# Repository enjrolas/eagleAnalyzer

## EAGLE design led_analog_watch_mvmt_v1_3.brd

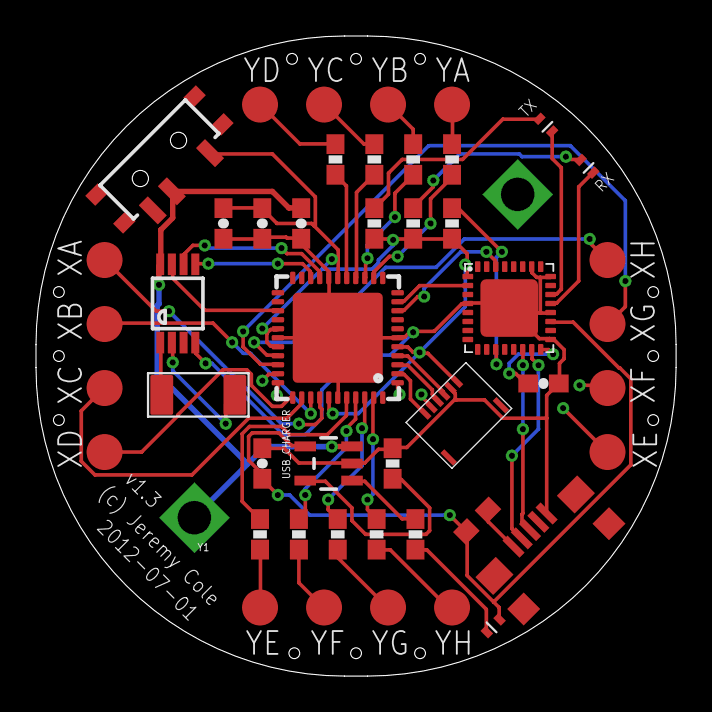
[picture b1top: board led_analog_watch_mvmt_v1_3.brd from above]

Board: 4 copper layers, 35.6 x 35.6 mm, 47 parts (1 on the bottom side), 51 nets.

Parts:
BAT1: 3V Li-Ion; BATTCON_245MM_PTH
C1, C2, C3, C4, C5: 0.1uF; 0603-CAP
CHLED: 0402
F1: 500mA; 0603
MCU: ATMEGA644M; MLF44-TH
R1, R11, R12: 330; 0603
R2, R3, R4, R5, R6, R7, R8, R9: 0603
R10, R13: 10k; 0603
RTC: DS1337UMAX; UMAX8
RXLED: 0402
S1: SWITCH-MA12R
TXLED: 0402
U$2: MOLEX_503480
USB_CHARGER: MCP73831; SOT23-5
USB_SERIAL: FT232RQ; QFN32
XA: TP20R
XB: TP20R
XC: TP20R
XD: TP20R
XE: TP20R
XF: TP20R
XG: TP20R
XH: TP20R
Y1: 32kHz; CRYSTAL-ABS10-SMD
YA: TP20R
YB: TP20R
YC: TP20R
YD: TP20R
YE: TP20R
YF: TP20R
YG: TP20R
YH: TP20R
µUSB: USB_MICROB_PLUG; USB_MICRO_B_TYCO

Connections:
GND: BAT1.2, C1.2, C2.2, C3.2, C4.2, C5.2, MCU.6, MCU.18, MCU.28, MCU.39, MCU.TH, R10.2, RTC.4, U$2.5, USB_CHARGER.2, USB_SERIAL.4, USB_SERIAL.17, USB_SERIAL.20, USB_SERIAL.24, USB_SERIAL.26, USB_SERIAL.EXP, µUSB.5
MISO: MCU.2, U$2.1
MOSI: MCU.1, U$2.2
unnamed: R1.2, USB_CHARGER.1
unnamed: R10.1, USB_CHARGER.5
unnamed: R2.2, YH.TP
unnamed: R3.2, YG.TP
unnamed: R4.2, YF.TP
unnamed: R5.2, YE.TP
unnamed: R6.2, YD.TP
unnamed: R7.2, YC.TP
unnamed: R8.2, YB.TP
unnamed: R9.2, YA.TP
unnamed: CHLED.2, R1.1
unnamed: R13.1, USB_SERIAL.11
unnamed: R12.1, RXLED.1
unnamed: RTC.2, Y1.X1
unnamed: RTC.1, Y1.X2
unnamed: R11.1, TXLED.1
unnamed: C5.1, USB_SERIAL.16
RST: MCU.4, U$2.4
RXD: MCU.9, USB_SERIAL.30
RXLED: RXLED.2, USB_SERIAL.21
SCK: MCU.3, U$2.3
SCL: MCU.19, RTC.6
SDA: MCU.20, RTC.5
SQW: MCU.25, RTC.7
TXD: MCU.10, USB_SERIAL.2
TXLED: TXLED.2, USB_SERIAL.22
USB_5V: C2.1, CHLED.1, F1.2, USB_CHARGER.4, USB_SERIAL.19
USB_N: USB_SERIAL.15, µUSB.2
USB_P: USB_SERIAL.14, µUSB.3
USB_UF: F1.1, µUSB.1
VBATT: BAT1.3, C1.1, RTC.8, S1.2, USB_CHARGER.3
VCC: C3.1, C4.1, MCU.5, MCU.17, MCU.27, MCU.29, MCU.38, R11.2, R12.2, R13.2, S1.3, U$2.6, USB_SERIAL.1
XA: MCU.37, XA.TP
XB: MCU.36, XB.TP
XC: MCU.35, XC.TP
XD: MCU.34, XD.TP
XE: MCU.33, XE.TP
XF: MCU.32, XF.TP
XG: MCU.31, XG.TP
XH: MCU.30, XH.TP
YA: MCU.13, R9.1
YB: MCU.14, R8.1
YC: MCU.15, R7.1
YD: MCU.16, R6.1
YE: MCU.40, R5.1
YF: MCU.41, R4.1
YG: MCU.42, R3.1
YH: MCU.43, R2.1

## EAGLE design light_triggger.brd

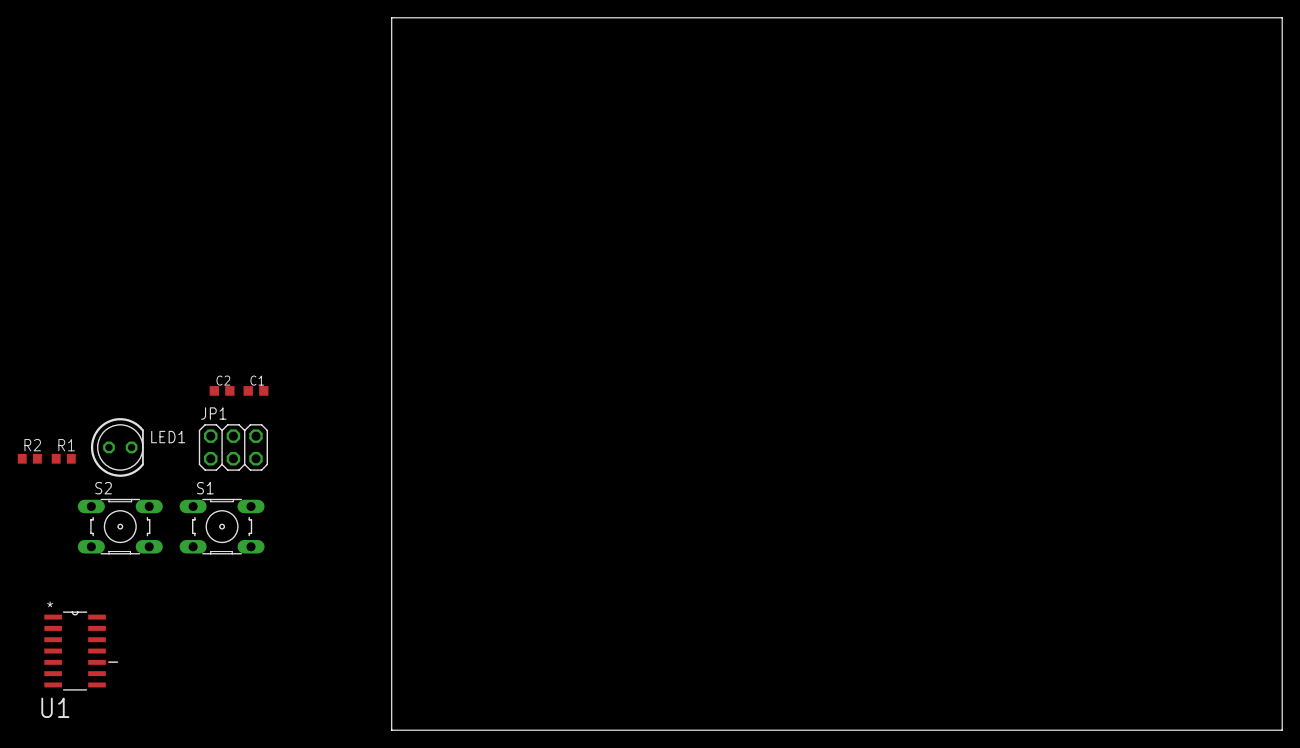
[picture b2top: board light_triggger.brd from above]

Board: 2 copper layers, 100.0 x 80.0 mm, 9 parts (0 on the bottom side), 8 nets, no tracks yet.

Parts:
C1, C2: C0603K
JP1: 2X03
LED1: LED5MM
R1, R2: R0603
S1, S2: B3F-10XX
U1: ATTINY24-20SSU; SOIC127P600X175-14N

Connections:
GND: C1.2, C2.2, JP1.6, S1.1, S1.2, S2.1, S2.2, U1.14
MISO: JP1.1, U1.5
MOSI: JP1.4, LED1.A, U1.3
unnamed: LED1.K, U1.8
unnamed: C2.1, R2.1, S2.3, S2.4, U1.7
RST: JP1.5, U1.4
SCK: C1.1, JP1.3, R1.1, S1.3, S1.4, U1.6
VCC: JP1.2, R1.2, R2.2, U1.1

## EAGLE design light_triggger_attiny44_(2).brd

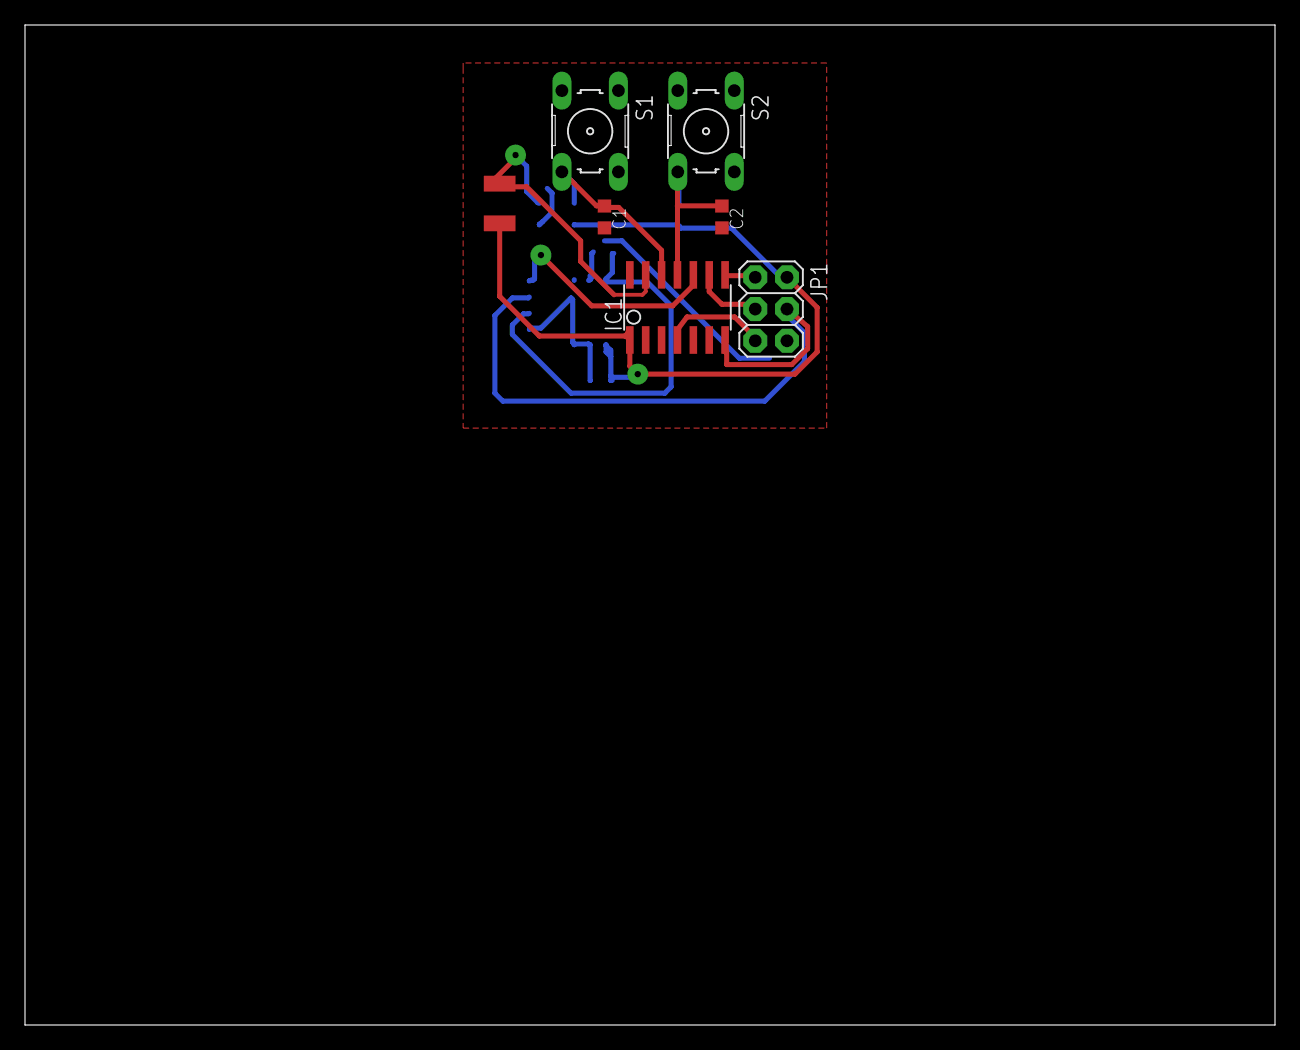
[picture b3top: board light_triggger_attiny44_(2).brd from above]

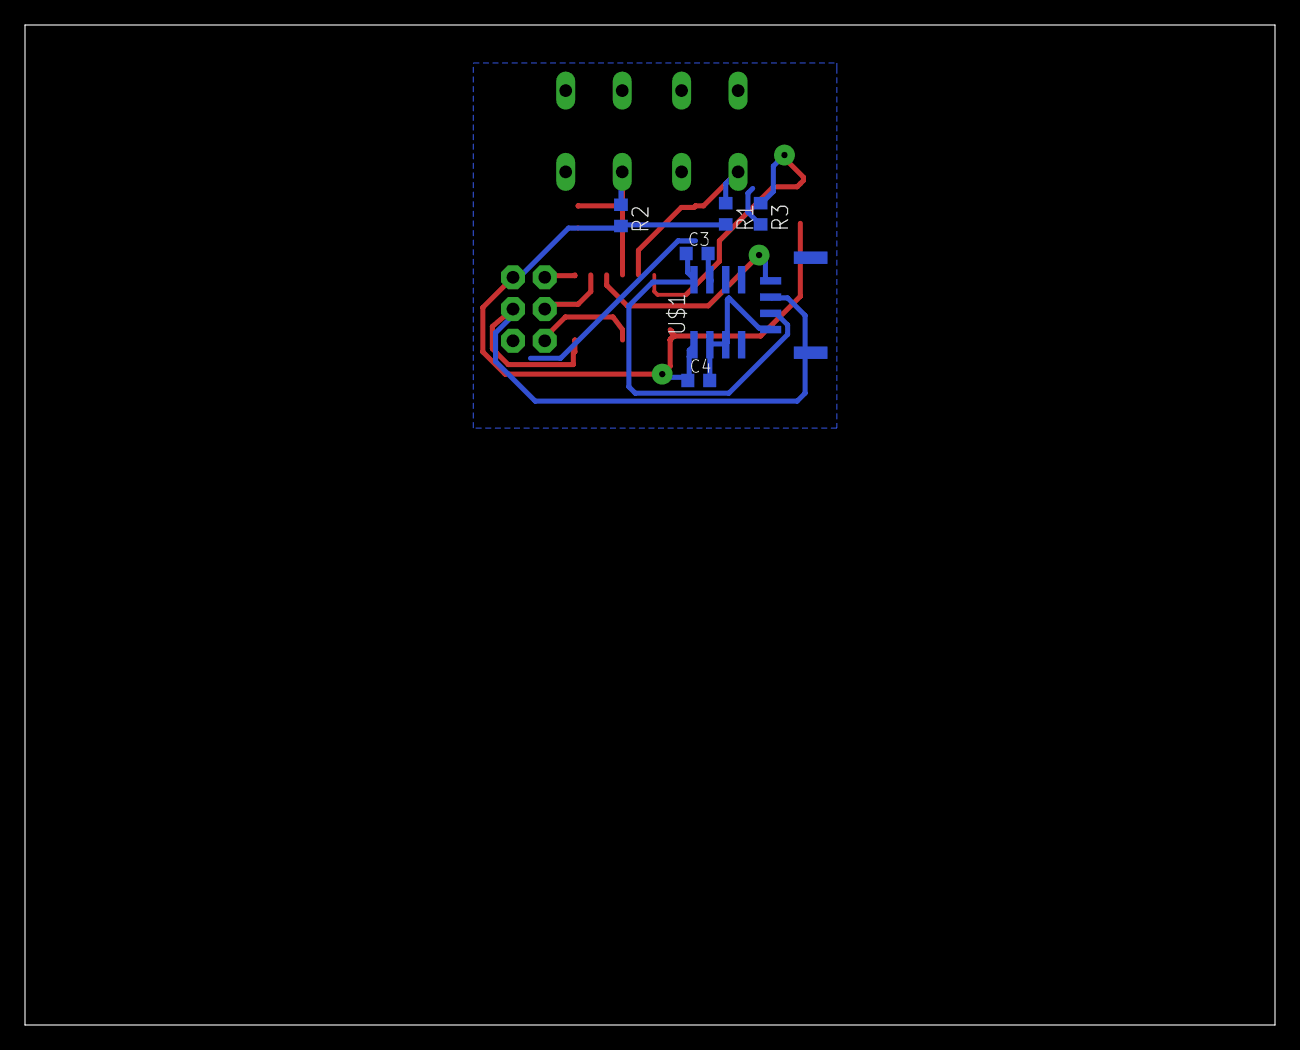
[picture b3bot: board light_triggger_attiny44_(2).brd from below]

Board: 2 copper layers, 100.0 x 80.0 mm, 14 parts (7 on the bottom side), 11 nets.

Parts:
C1, C2, C3, C4: C0603K
IC1: ATTINY24/44/84-SSU; SOIC14
JP1: 2X03
R1, R2, R3: R0603
S1, S2: B3F-10XX
U$1: LM78L05
U$2: 0P525DA; PHOTOTRANSITOR(OP525DA)
U$3: SM04B-GHS-TB

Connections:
GND: C1.2, C2.2, C3.2, C4.2, IC1.14, JP1.6, R3.2, S1.2, S2.2, U$1.2, U$1.3, U$1.6, U$1.7, U$3.GND
MISO: IC1.8, JP1.1
MOSI: IC1.7, JP1.4, U$3.PWMLED
unnamed: IC1.13, R3.1, U$2.P$2
unnamed: IC1.10, U$3.TIMLED
unnamed: C1.1, IC1.12, R1.1, S1.4
unnamed: C2.1, IC1.11, R2.1, S2.4
RST: IC1.4, JP1.5
SCK: IC1.9, JP1.3
VCC: C4.1, IC1.1, JP1.2, R1.2, R2.2, U$1.1, U$2.P$1
VIN: C3.1, U$1.8, U$3.VIN

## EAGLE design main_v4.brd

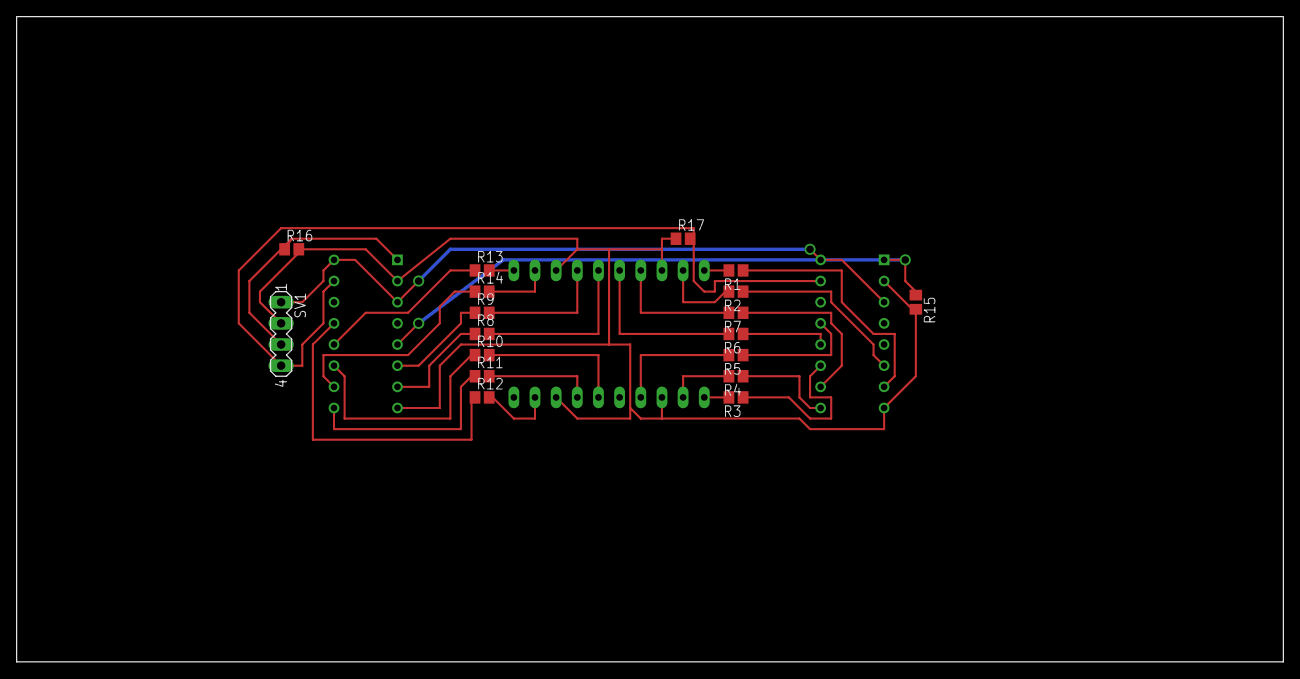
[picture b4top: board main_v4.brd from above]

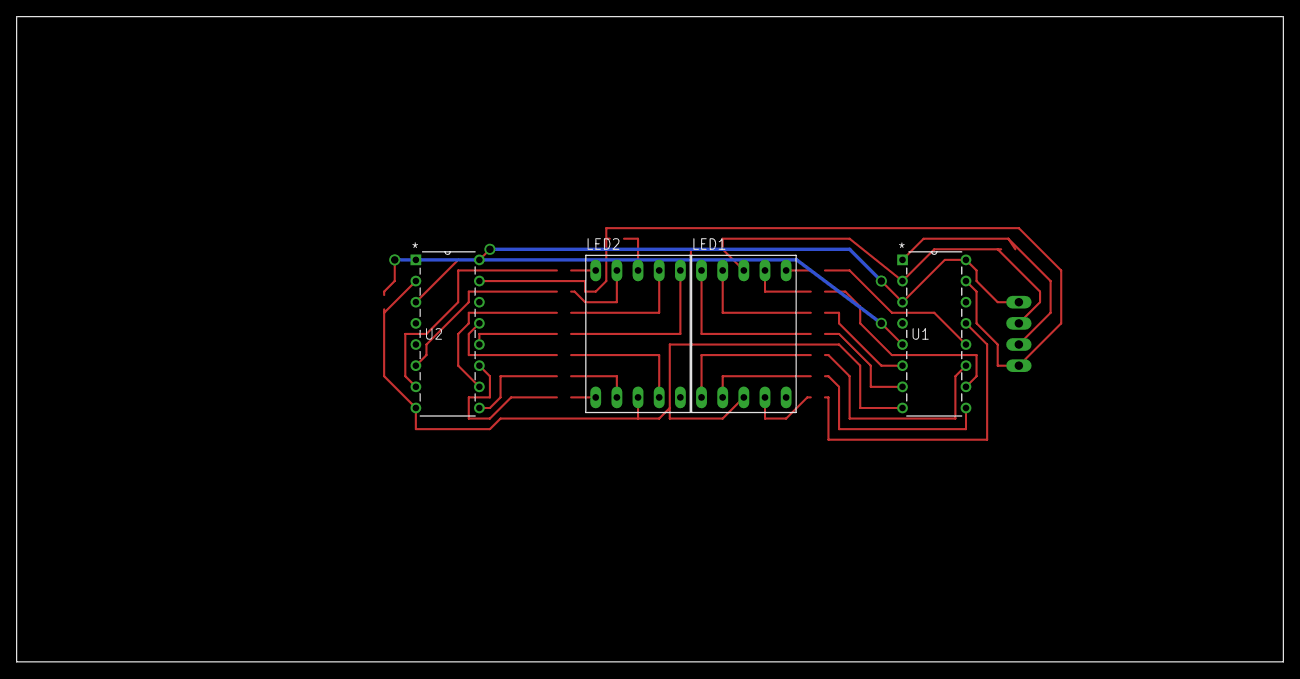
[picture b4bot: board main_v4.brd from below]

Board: 2 copper layers, 152.1 x 77.5 mm, 22 parts (4 on the bottom side), 33 nets.

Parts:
LED1, LED2: 7-SEG_SA56-11; SA56-11
R1, R2, R3, R4, R5, R6, R7, R8, R9, R10, R11, R12, R13, R14: 220; R0805
R15, R16, R17: 10K; R0805
SV1: +5, 0, clock, reset; MA04-1
U1, U2: CD4026B_N_16; N16

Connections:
unnamed: LED2.10, R1.2
unnamed: LED2.9, R2.2
unnamed: LED2.1, R3.2
unnamed: LED2.2, R4.2
unnamed: LED2.4, R5.2
unnamed: LED2.6, R6.2
unnamed: LED2.7, R7.2
unnamed: SV1.1, U1.3, U1.16, U2.3, U2.16
unnamed: LED1.3, LED1.8, LED2.3, LED2.8, R15.2, R16.2, R17.1, SV1.2, U1.2, U1.8, U2.2, U2.8
unnamed: LED1.10, R8.2
unnamed: LED1.9, R9.2
unnamed: LED1.1, R10.2
unnamed: LED1.2, R11.2
unnamed: LED1.4, R12.2
unnamed: LED1.6, R13.2
unnamed: LED1.7, R14.2
unnamed: R16.1, SV1.3, U1.1
unnamed: R7.1, U2.10
unnamed: R6.1, U2.12
unnamed: R17.2, SV1.4, U1.15, U2.15
unnamed: R5.1, U2.13
unnamed: R4.1, U2.9
unnamed: R3.1, U2.11
unnamed: R2.1, U2.6
unnamed: R1.1, U2.7
unnamed: R15.1, U1.5, U2.1
unnamed: R9.1, U1.6
unnamed: R8.1, U1.7
unnamed: R12.1, U1.13
unnamed: R13.1, U1.12
unnamed: R10.1, U1.11
unnamed: R14.1, U1.10
unnamed: R11.1, U1.9

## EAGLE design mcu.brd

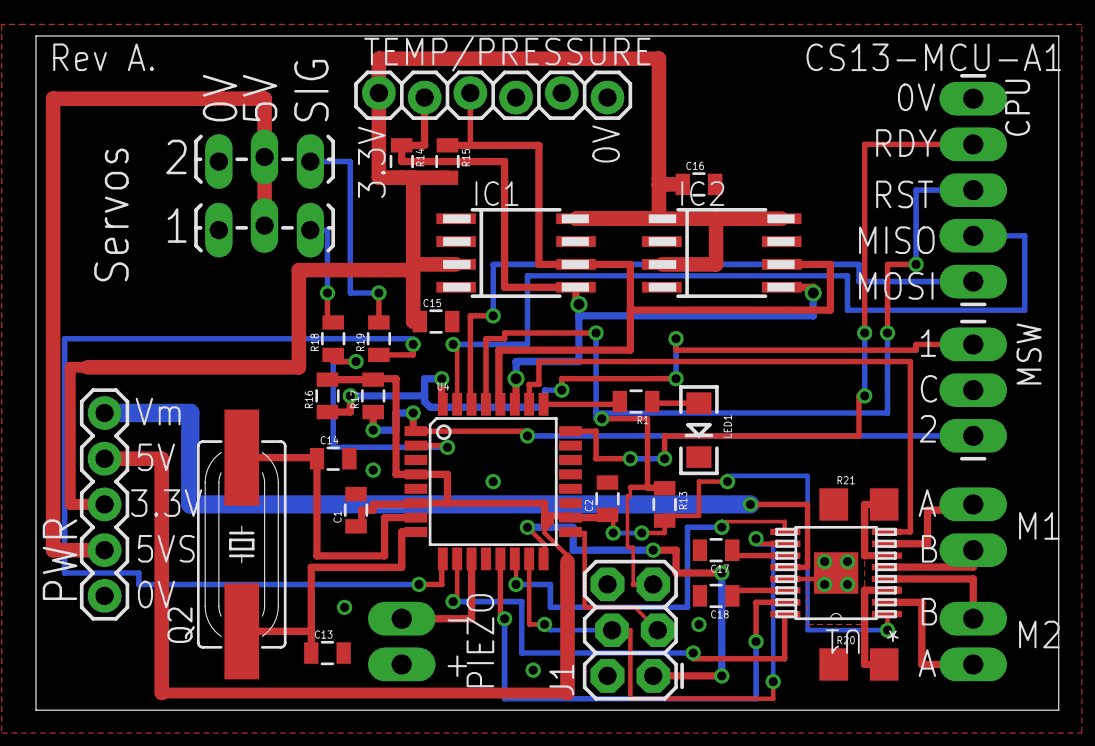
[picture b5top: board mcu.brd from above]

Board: 2 copper layers, 56.8 x 37.5 mm, 34 parts (0 on the bottom side), 37 nets.

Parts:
C1, C2: 1uF; 0805
C13, C14: 18p; 0805
C15, C16: 1u; 0805
C17: 0.01u; 0805
C18: 2.2u; 0805
CPU: 1X05_LONGPADS
IC1, IC2: 24LC128SM; SO-08M
J1: AVR_SPI_PRG_62X3_LOCK; 2X3_LOCK
JP1: 1X02_LONGPADS
JP2, JP3: 1X03_LOCK_LONGPADS
LED1: LED-1206
M1, M2: 1X02_LONGPADS
MCU_PWR: 1X05
MSW: 1X03_LONGPADS
Q2: 16M; HC49UP
R1: 330; 0805
R13: 100k; 0805
R14, R15: 2.2k; 0805
R16, R17: 10k; 0805
R18, R19: 100; 0805
R20, R21: 0.1; 1206
TPS: 1X06_LOCK
U1: DRV8833_PWP_16; PWP16_2P31X2P46
U4: ATMEGA328P; TQFP32-08

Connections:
3.3V: C15.1, C16.1, IC1.3, IC1.8, IC2.1, IC2.3, IC2.8, MCU_PWR.3, R14.2, R15.2, TPS.1
5V: C1.1, C2.1, MCU_PWR.4, R13.2, R16.2, R17.2, U1.1, U4.4, U4.6, U4.18
5VS: JP2.2, JP3.2, MCU_PWR.2
FLT: U1.8, U4.26
GND: C1.2, C2.2, C13.2, C14.2, C15.2, C16.2, C17.2, C18.2, CPU.1, IC1.1, IC1.2, IC1.4, IC1.7, IC2.2, IC2.4, IC2.7, J1.6, JP1.2, JP2.3, JP3.3, LED1.C, MCU_PWR.1, MSW.2, R20.1, R21.1, TPS.6, U1.13, U1.EPAD, U4.3, U4.5, U4.21
LNK_MISO: CPU.4, U4.31
LNK_MOSI: CPU.5, U4.30
M1A: M1.1, U1.2
M1A_CTL: U1.16, U4.10
M1B: M1.2, U1.4
M1B_CTL: U1.15, U4.13
M2A: M2.1, U1.7
M2A_CTL: U1.9, U4.14
M2B: M2.2, U1.5
M2B_CTL: J1.4, U1.10, U4.15
unnamed: LED1.A, R1.1
unnamed: JP2.1, R18.2
unnamed: J1.3, U4.17
unnamed: J1.1, U4.16
unnamed: JP3.1, R19.2
unnamed: C17.1, U1.11
unnamed: C18.1, U1.14
unnamed: R21.2, U1.6
unnamed: R20.2, U1.3
PIEZO: JP1.1, U4.11
RDY: CPU.2, U4.24
RST: CPU.3, J1.5, R13.1, U4.29
SCL: IC1.6, IC2.6, R15.1, TPS.3, U4.28
SDA: IC1.5, IC2.5, R14.1, TPS.2, U4.27
SERVO1: R18.1, U4.2
SERVO2: R19.1, U4.9
STAT: R1.2, U4.25
SW1: MSW.1, R16.1, U4.32
SW2: MSW.3, R17.1, U4.1
V_BATT: MCU_PWR.5, U1.12
XTAL1: C14.1, Q2.2, U4.7
XTAL2: C13.1, Q2.1, U4.8

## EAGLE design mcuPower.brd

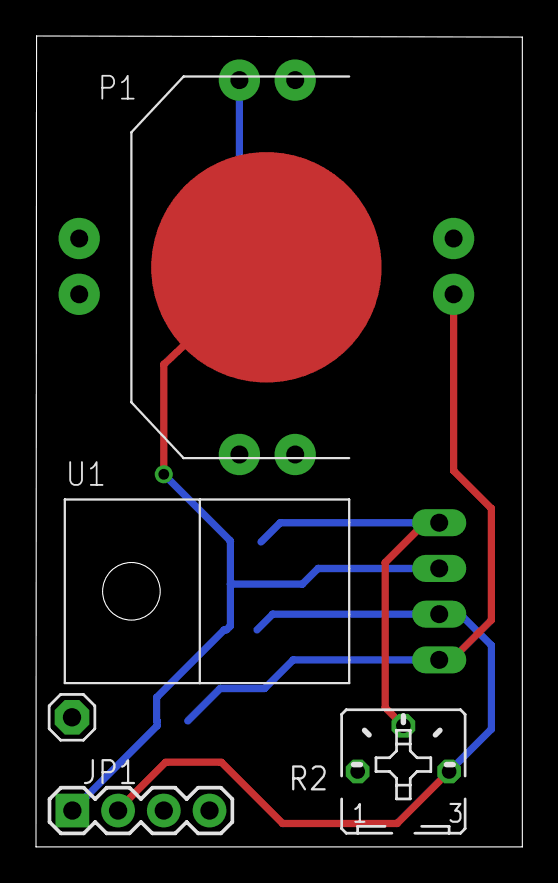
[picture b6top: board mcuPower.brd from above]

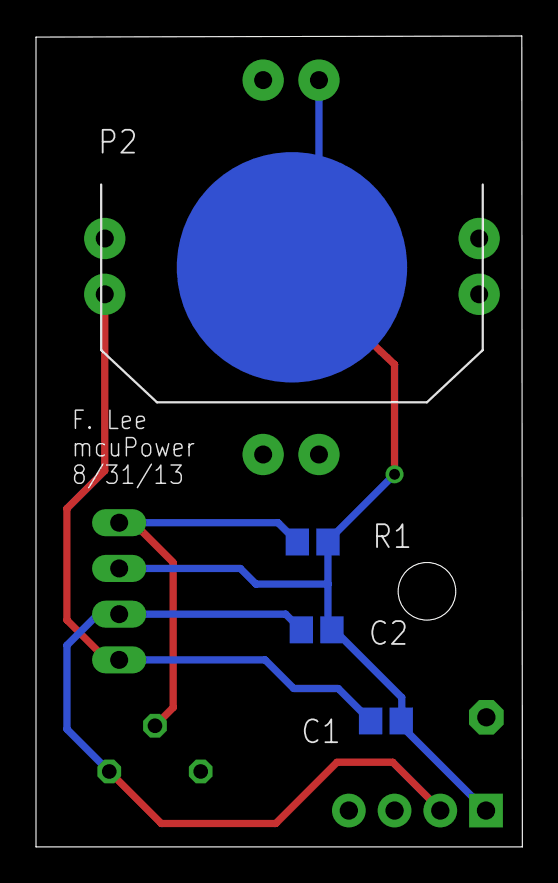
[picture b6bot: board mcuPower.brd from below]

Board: 2 copper layers, 27.0 x 45.0 mm, 9 parts (4 on the bottom side), 5 nets.

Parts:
C1, C2: C0805
JP1: 1X04
JP2: 1X01
P1, P2: CR2032; CR2032/2025
R1: R0805
R2: B25P
U1: PQ070XF01SZH; TO220-4

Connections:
GND: C1.2, C2.2, JP1.1, P1.GND, R1.2, U1.GND
unnamed: P1.VCC_3, P2.GND
unnamed: R1.1, R2.S, U1.VADJ
VCC: C1.1, P2.VCC_3, U1.VIN
VOUT: C2.1, JP1.2, R2.E, U1.VOUT

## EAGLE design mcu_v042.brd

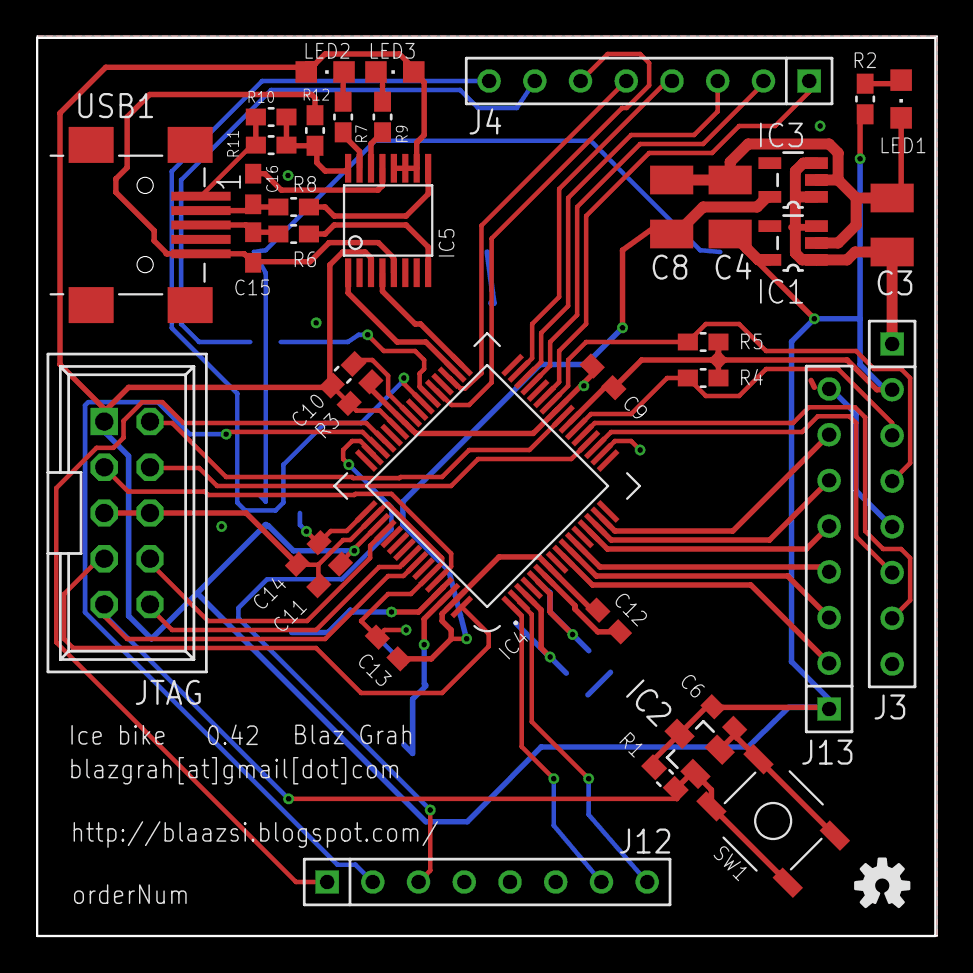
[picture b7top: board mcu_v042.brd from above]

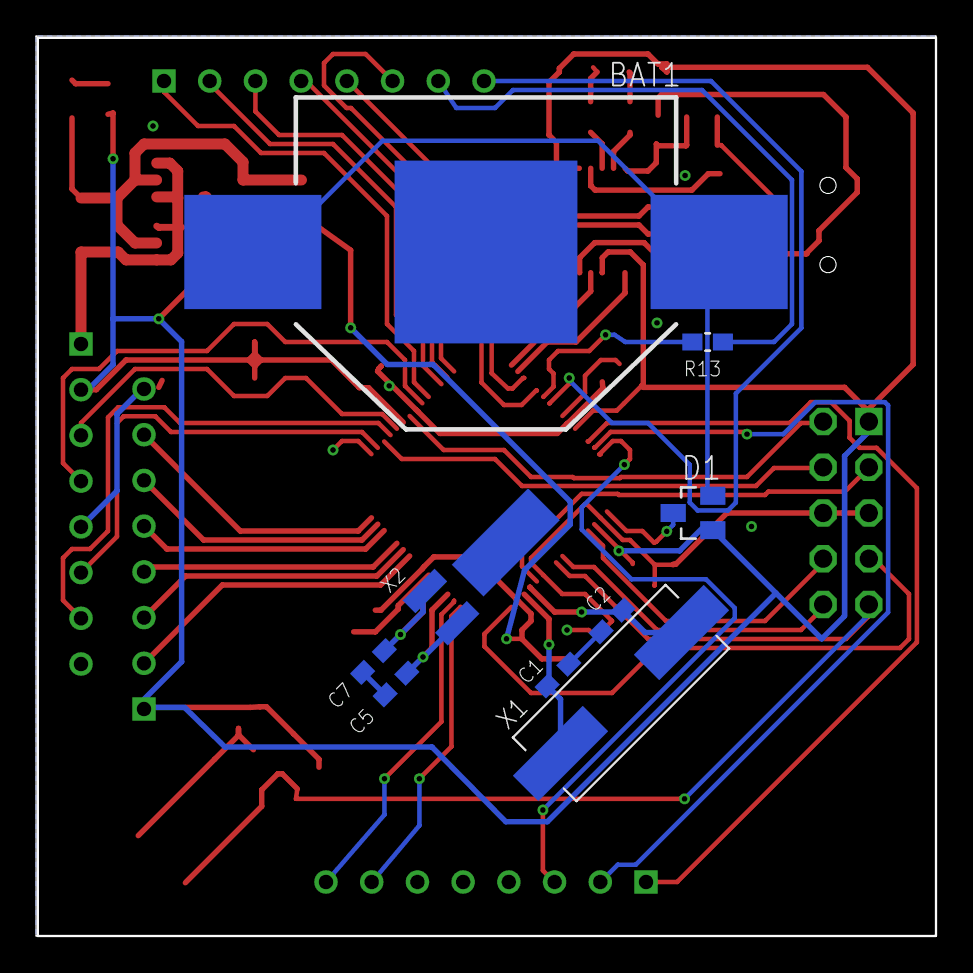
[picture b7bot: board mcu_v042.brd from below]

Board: 2 copper layers, 50.0 x 50.0 mm, 51 parts (9 on the bottom side), 55 nets.

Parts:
BAT1: CR2032; BATTERY_20MM_SMD
C1, C2: 39p; C0603
C3: 22u/10V; SMC_B
C4, C8: 47u/6.3V; SMC_B
C5, C7: 22p; C0603
C6, C9, C10, C11, C12, C13, C14: 100n; C0603
C15, C16: 47p; C0603
D1: BAT54C; SOT23
DOC: FRAME_DINA4_L; DP_LOGO
IC1, IC3: SP6205_3V3_VREG; SOT23-5
IC2: MCP111T_300; SOT23
IC4: LPC2138; LQFP64
IC5: FT230XS_FTDI; SSOP16
J3, J4, J12, J13: CON_HEADER_1X08-PTH; M1X8
JTAG: CON_HEADER_2X05-PTH+SHROUDED_A; PINSHRD_PTH_2X05
LED1: RED; LED0805
LED2, LED3: GREEN; LED0805
LOGO1: OSHW-LOGOS; OSHW-LOGO-S
PCB1: PCB; PCB_50X50
R1, R3, R10, R11, R12: 10K; R0603
R2, R7, R9: 330; R0603
R4, R5: 4K7; R0603
R6, R8: 27; R0603
R13: 0R; R0603
SW1: RST; BUTTON_SW_4P_SMD
USB1: CON-USB-F-MINI-B; CONN_USB_MINI-B
X1: 12M; CRYSTAL_12M_4.8X10.6MM
X2: 32K; CRYSTAL_32K_SMD

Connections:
3V3: C4.+, C6.1, C9.1, C10.1, C11.1, D1.1, IC1.5, IC2.3, IC4.23, IC4.43, IC4.51, IC5.P$3, IC5.P$10, IC5.P$11, IC5.P$12, J3.2, J13.1, JTAG.1, LED2.A, LED3.A, R1.2, R2.2, R3.2, R4.2, R5.2
5V: C3.+, IC1.1, IC1.3, IC3.1, IC3.3, J3.1
BSL: IC4.41, R3.1
GND: BAT1.NEG, C1.1, C2.1, C3.-, C4.-, C5.1, C6.2, C7.1, C8.-, C9.2, C10.2, C11.2, C12.2, C13.2, C14.2, C15.2, C16.2, IC1.2, IC2.2, IC3.2, IC4.6, IC4.18, IC4.25, IC4.42, IC4.50, IC4.59, IC5.P$5, IC5.P$13, J3.5, J3.8, J12.4, J12.5, J12.6, J13.8, JTAG.5, JTAG.6, LED1.C, R12.1, SW1.1, SW1.2, USB1.GND
unnamed: LED1.A, R2.1
unnamed: BAT1.POS1, BAT1.POS2, D1.2
unnamed: C16.1, R8.1, USB1.D-
unnamed: C15.1, R6.1, USB1.D+
unnamed: IC5.P$9, R8.2
unnamed: IC5.P$8, R6.2
unnamed: R10.2, R11.2, USB1.VUSB
unnamed: IC5.P$16, R10.1, R11.1, R12.2
unnamed: IC5.P$14, R9.1
unnamed: LED2.C, R7.2
unnamed: LED3.C, R9.2
unnamed: IC5.P$15, R7.1
P0.4: IC4.27, J4.1
P0.5: IC4.29, J4.2
P0.6: IC4.30, J4.3
P0.7: IC4.31, J4.4
P0.10: IC4.35, J4.5
P0.11: IC4.37, J4.6
P0.12: IC4.38, R13.1
P0.12A: J4.7, R13.2
P0.13: IC4.39, J4.8
P0.15: IC4.45, J12.1
P0.16: IC4.46, J12.2
P0.17: IC4.47, J12.3
P0.21: IC4.1, J12.7
P0.22: IC4.2, J12.8
P0.25: IC4.9, J13.2
P0.26: IC4.10, J13.3
P0.27: IC4.11, J13.4
P0.28: IC4.13, J13.5
P0.29: IC4.14, J13.6
P0.30: IC4.15, J13.7
RST: IC2.1, IC4.57, JTAG.9, R1.1, SW1.3, SW1.4
RTCK: IC4.24, JTAG.2
RTXC1: C5.2, IC4.3, X2.X2
RTXC2: C7.2, IC4.5, X2.X1
RXD0: IC4.21, J3.7
RXD1: IC4.34, IC5.P$1
SCL0: IC4.22, J3.3, R4.1
SDA0: IC4.26, J3.4, R5.1
TCK: IC4.56, JTAG.10
TDI: IC4.60, JTAG.3
TDO: IC4.64, JTAG.7
TMS: IC4.52, JTAG.8
TRST: IC4.20, JTAG.4
TXD0: IC4.19, J3.6
TXD1: IC4.33, IC5.P$4
VBAT: C14.1, D1.3, IC4.49
VDDA: C8.+, C12.1, C13.1, IC3.5, IC4.7, IC4.63
XTAL1: C1.2, IC4.62, X1.P$2
XTAL2: C2.2, IC4.61, X1.P$1

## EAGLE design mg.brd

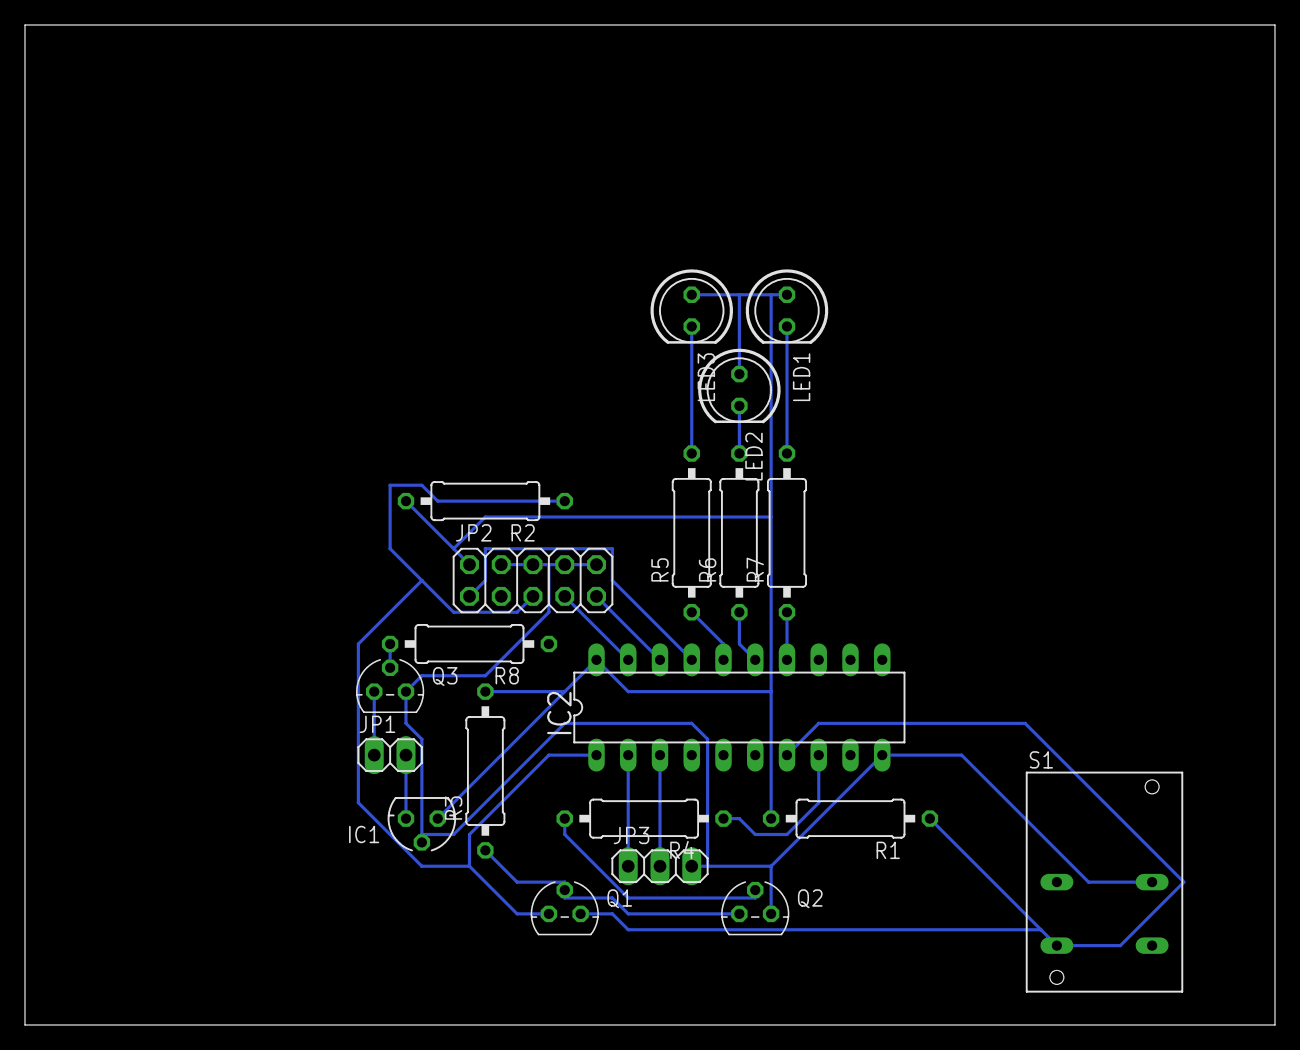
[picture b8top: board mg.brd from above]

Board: 2 copper layers, 100.0 x 80.0 mm, 20 parts (0 on the bottom side), 22 nets.

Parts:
IC1: 78L05; 78LXX
IC2: AT90S2313P; DIL20
JP1: 1X02
JP2: 2X05
JP3: 1X03
LED1, LED2, LED3: LED5MM
Q1, Q2, Q3: BC238; TO92
R1, R2, R3, R4, R8: 10k; 0309/12
R5, R6, R7: 500; 0309/12
S1: SRK

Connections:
!RESET: IC2.1, JP2.5, Q1.3, R2.1
+5V: IC1.OUT, IC2.20, JP2.2, LED1.A, LED2.A, LED3.A, R1.2, R2.2, R3.2
+18V: IC1.IN, JP1.2
GND: IC1.GND, IC2.10, JP2.4, JP2.6, JP2.8, JP2.10, JP3.3, Q2.1, Q3.1, S1.3
MISO: IC2.18, JP2.9
MOSI: IC2.17, JP2.1
unnamed: Q1.2, Q2.3, R3.1
unnamed: IC2.7, Q1.1, R1.1, S1.1
unnamed: Q2.2, R4.2
unnamed: IC2.9, R8.1
unnamed: IC2.16, R5.1
unnamed: IC2.15, R6.1
unnamed: LED3.K, R5.2
unnamed: IC2.14, R7.1
unnamed: Q3.2, R8.2
unnamed: JP1.1, Q3.3
unnamed: LED2.K, R6.2
unnamed: LED1.K, R7.2
unnamed: IC2.8, R4.1
unnamed: IC2.3, JP3.2
unnamed: IC2.2, JP3.1
SCK: IC2.19, JP2.7

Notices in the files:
mcu_v042.brd:
LICENSE: OSHW
parts and their libraries:
SparkFun-Connectors: Licensing: CC v3.0 Share-Alike You are welcome to use this library for commercial purposes.
